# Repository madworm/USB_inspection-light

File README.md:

USB inspection-light
====================

LAYOUT FILES: USB powered inspection light for tight places.

You will find code for this project in [this](https://github.com/madworm/ATtiny_projects) repository.

---

Before having PC-boards made, please make sure you know about your manufacturer's peculiarities!
Especially drill-sizes and their tolerances may vary too much and give you trouble.

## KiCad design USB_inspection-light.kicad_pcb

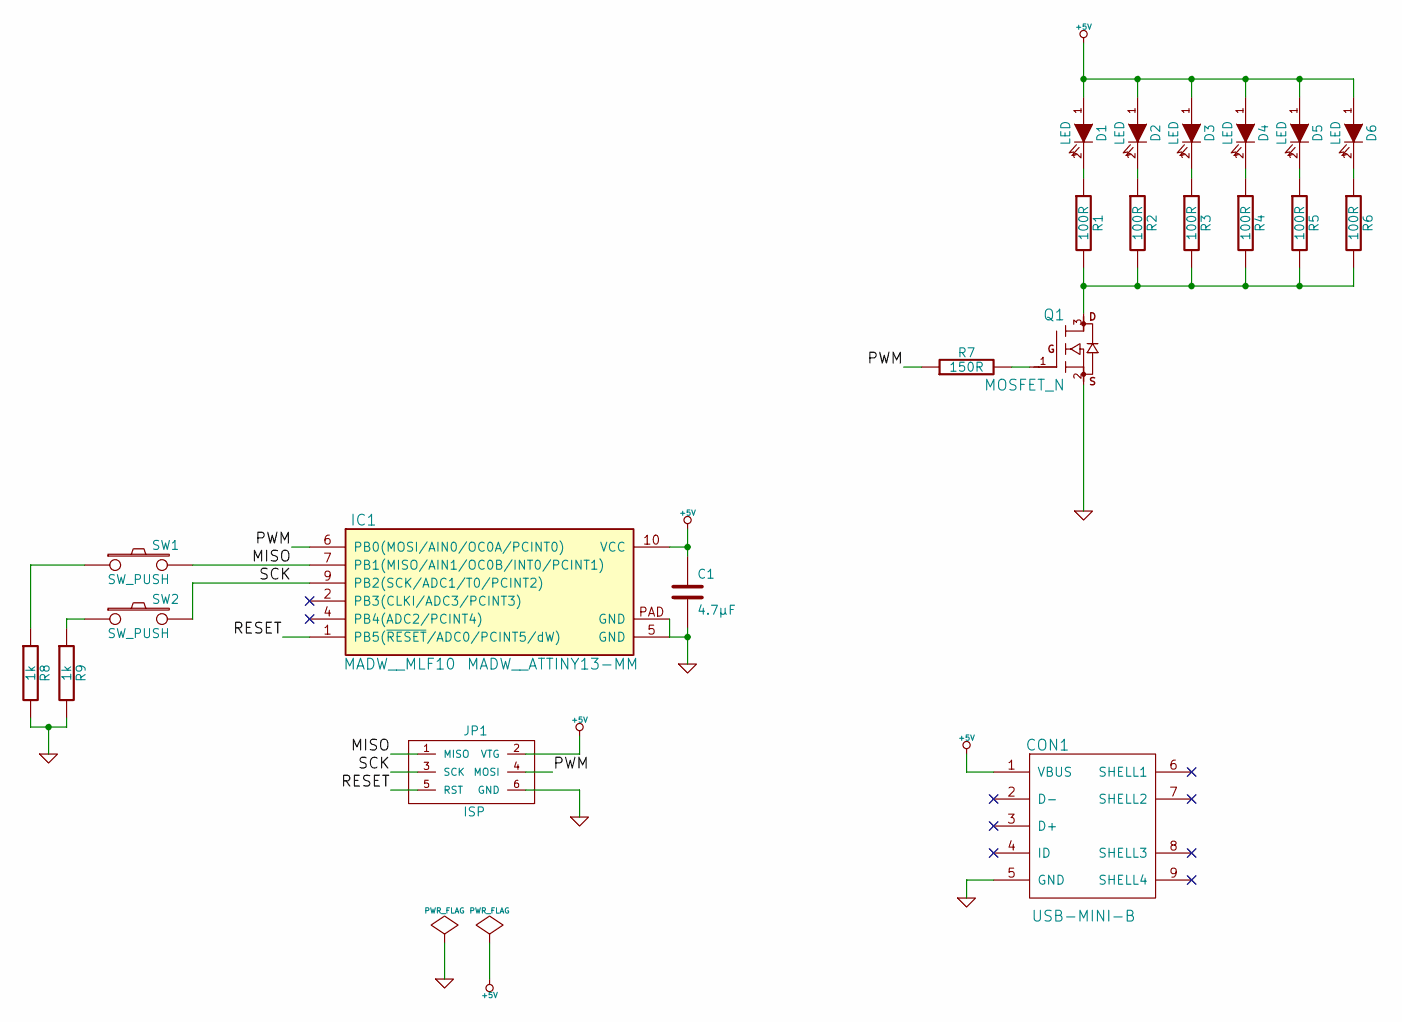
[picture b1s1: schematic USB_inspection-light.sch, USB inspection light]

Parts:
C1: 4.7µF
CON1: USB-MINI-B
D1, D2, D3, D4, D5, D6: LED
IC1: MADW__ATTINY13-MM; MADW__MLF10
JP1: ISP
Q1: MOSFET_N
R1, R2, R3, R4, R5, R6: 100R
R7: 150R
R8, R9: 1k
SW1, SW2: SW_PUSH

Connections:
+5V: C1.1, CON1.1 (VBUS), D1.1 (A), D2.1 (A), D3.1 (A), D4.1 (A), D5.1 (A), D6.1 (A), IC1.10 (VCC), JP1.2 (VTG)
/MISO: IC1.7 (PB1(MISO/AIN1/OC0B/INT0/PCINT1)), JP1.1 (MISO), SW1.2
/PWM: IC1.6 (PB0(MOSI/AIN0/OC0A/PCINT0)), JP1.4 (MOSI), R7.1
/RESET: IC1.1 (PB5(~RESET~/ADC0/PCINT5/dW)), JP1.5 (RST)
/SCK: IC1.9 (PB2(SCK/ADC1/T0/PCINT2)), JP1.3 (SCK), SW2.2
GND: C1.2, CON1.5 (GND), IC1.5 (GND), IC1.PAD (GND), JP1.6 (GND), Q1.2 (S), R8.2, R9.2; also elsewhere on the board
unnamed: D1.2 (K), R1.1
unnamed: D2.2 (K), R2.1
unnamed: D3.2 (K), R3.1
unnamed: D4.2 (K), R4.1
unnamed: D5.2 (K), R5.1
unnamed: D6.2 (K), R6.1
unnamed 23: Q1.1 (G), R7.2; also elsewhere on the board
unnamed: Q1.3 (D), R1.2, R2.2, R3.2, R4.2, R5.2, R6.2
unnamed: R8.1, SW1.1
unnamed: R9.1, SW2.1

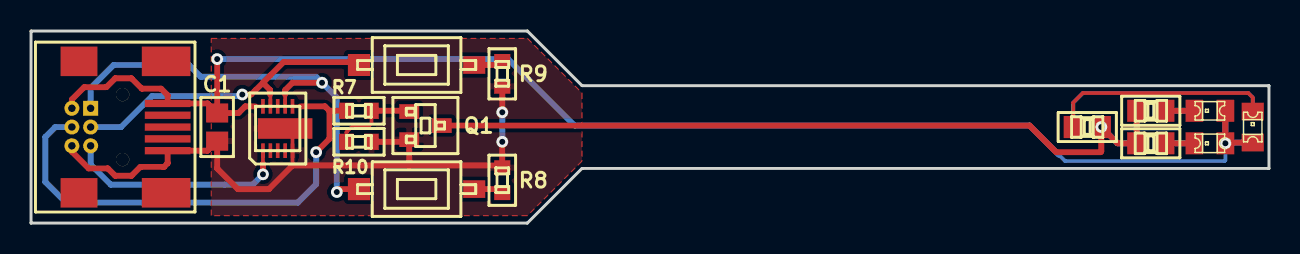
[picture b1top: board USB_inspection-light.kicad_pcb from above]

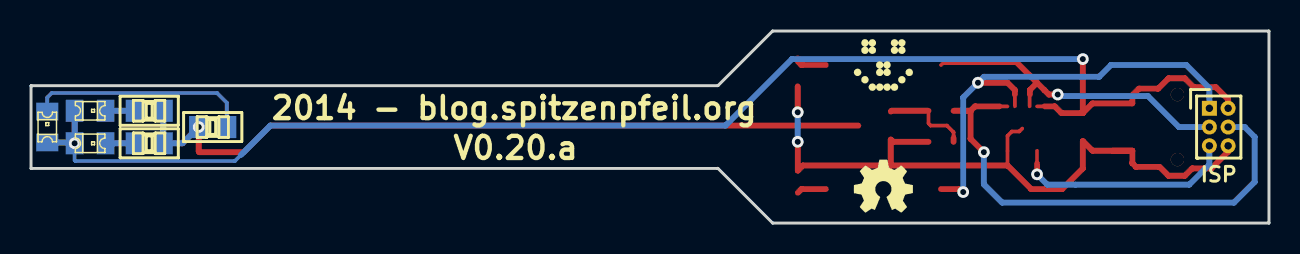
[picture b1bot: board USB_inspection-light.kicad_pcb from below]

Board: 2 copper layers, 83.8 x 13.0 mm, 25 parts (9 on the bottom side), 16 nets.

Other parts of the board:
G1: OSHW-logo_silkscreen_4mm
G2: LED_smile_silkscreen_4mm
R10: 100k; MADW__R0603_2

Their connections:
GND: R10.1; also elsewhere on the board
unnamed 23: R10.2; also elsewhere on the board

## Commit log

2014-02-23 Added 3D shapes.
    Thanks to: http://smisioto.no-ip.org/elettronica/kicad/kicad-en.htm
2014-03-02 Added a GND plane on F_Cu. Just for fun.
2014-03-03 GND plane tweaks.
2014-03-14 Adapted board outline to changed usb socket footprint outline.
2014-03-16 Switched SOT23 footprint to my own library. Silkscreen issue.
2014-03-16 Updated 'README.md'.
2014-03-18 Tweaks: incr. trace-width, ISP header, copper pour.
2014-05-06 Added 100k pull-down resistor to mosfet gate.
    Purpose: prevent LED flash on power-up.
2014-05-27 Updated 'gerber_files/make_all-pngs.sh'.
2014-09-19 Added 'ERRATA.txt'.
